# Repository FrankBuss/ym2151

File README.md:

# YM2151 board for C64 and Arduino

## Original Z80 project
https://github.com/kuninet/Z80_YM2151

## C64 Sound Expander circuit diagram
https://www.c64-wiki.de/images/0/0f/Commodore_Sound_Expander_Schematic_SVG.svg

## Parts
TRS connector: https://www.tme.eu/en/details/acjs-nh35/jack-connectors/amphenol/

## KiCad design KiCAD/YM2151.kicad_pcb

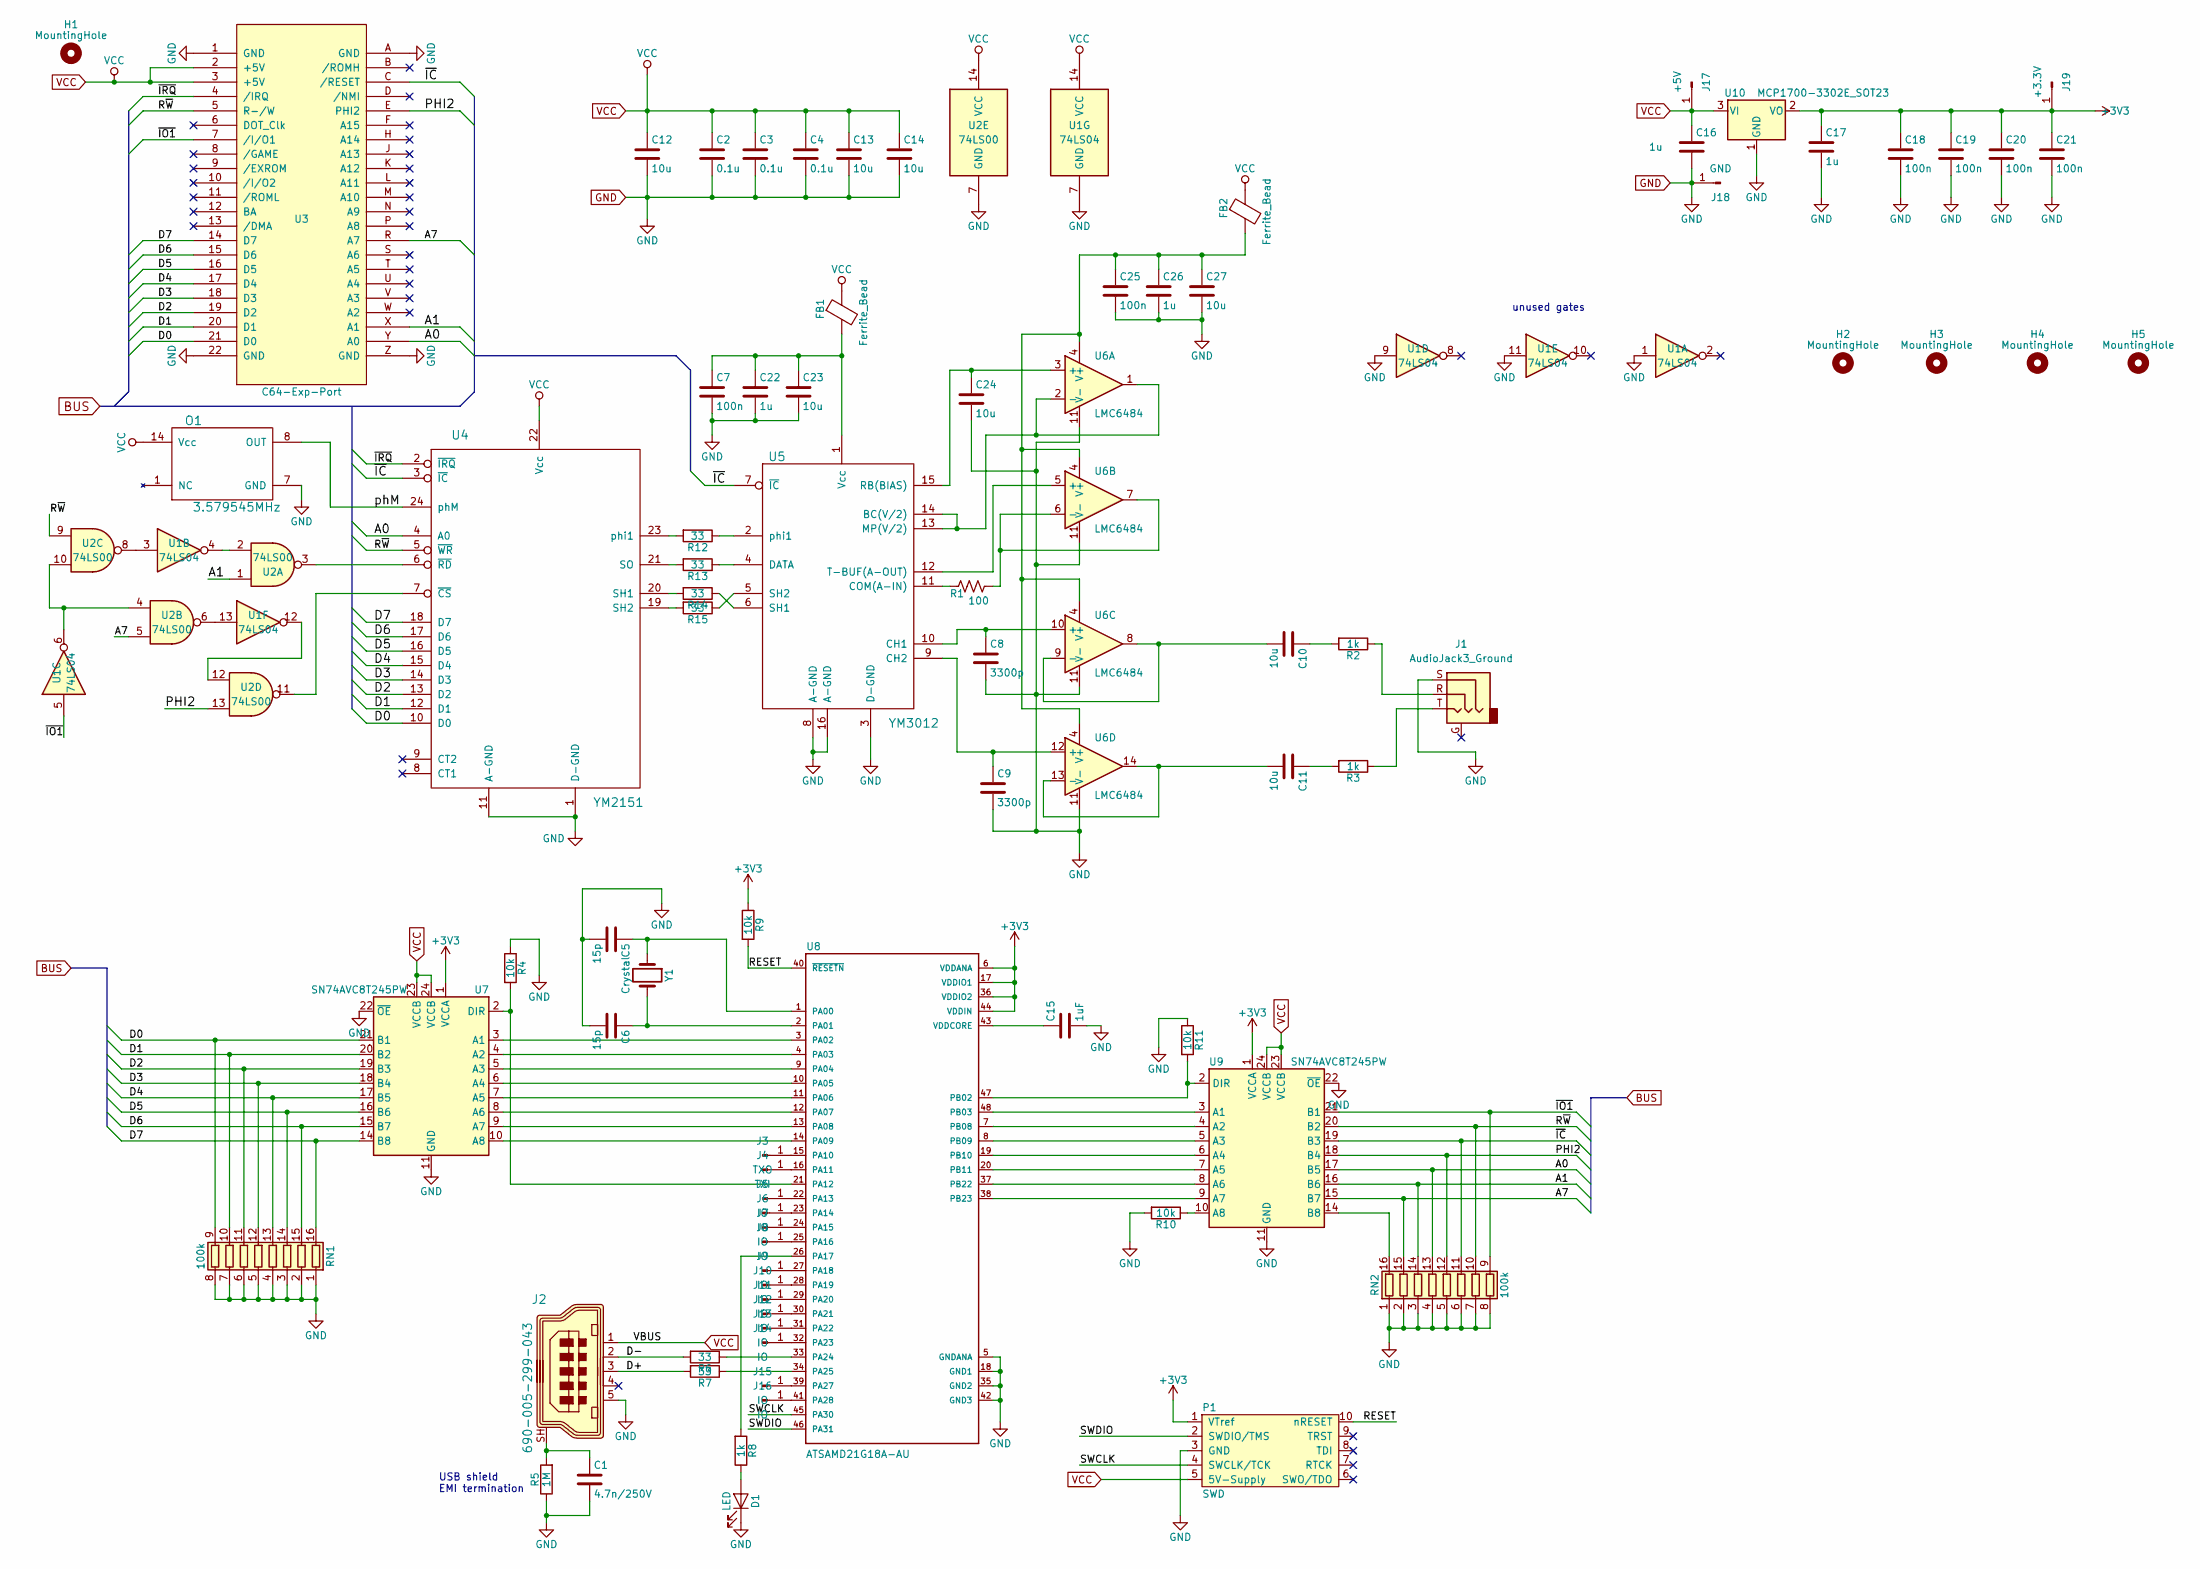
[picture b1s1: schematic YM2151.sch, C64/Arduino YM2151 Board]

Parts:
C1: 4.7n/250V; C_0805_2012Metric
C2, C3, C4: 0.1u; C_0805_2012Metric
C5, C6: 15p; C_0805_2012Metric
C7, C18, C19, C20, C21, C25: 100n; C_0805_2012Metric
C8, C9: 3300p; C_0805_2012Metric
C10, C11, C12, C13, C14, C23, C24, C27: 10u; C_0805_2012Metric
C15: 1uF; C_0805_2012Metric
C16, C17, C22, C26: 1u; C_0805_2012Metric
D1: LED; LED_0805_2012Metric
FB1, FB2: Ferrite_Bead; L_1206_3216Metric
H1, H2, H3, H4, H5: MountingHole; MountingHole_3.2mm_M3
J1: AudioJack3_Ground; trs
J2: 690-005-299-043; USB_Mini_B_Female_690-005-299-043; MPN 690-005-299-043; Digi-Key_PN 151-1206-1-ND
J3: TXO; PinHeader_1x01_P2.54mm_Vertical
J4: TXI; PinHeader_1x01_P2.54mm_Vertical
J5, J6, J7, J8, J9, J10, J11, J12, J13, J14, J15, J16: IO; PinHeader_1x01_P2.54mm_Vertical
J17: +5V; PinHeader_1x01_P2.54mm_Vertical
J18: GND; PinHeader_1x01_P2.54mm_Vertical
J19: +3.3V; PinHeader_1x01_P2.54mm_Vertical
O1: 3.579545MHz; DIP-14_W7.62mm_Socket_LongPads
P1: SWD; swd
R1: 100; R_0805_2012Metric
R2, R3, R8: 1k; R_0805_2012Metric
R4, R9, R10, R11: 10k; R_0805_2012Metric
R5: 1M; R_0805_2012Metric
R6, R7, R12, R13, R14, R15: 33; R_0805_2012Metric
RN1, RN2: 100k; R_Array_Convex_8x0602
U1: 74LS04; SOIC-14_3.9x8.7mm_P1.27mm
U2: 74LS00; SOIC-14_3.9x8.7mm_P1.27mm
U3: C64-Exp-Port; C64-Cart
U4: YM2151; DIP-24_W15.24mm_LongPads
U5: YM3012; DIP-16_W7.62mm_Socket_LongPads
U6: LMC6484; SOIC-14_3.9x8.7mm_P1.27mm
U7, U9: SN74AVC8T245PW; TSSOP-24_4.4x7.8mm_P0.65mm
U8: ATSAMD21G18A-AU; QFP50P900X900X120-48N
U10: MCP1700-3302E_SOT23; SOT-23
Y1: Crystal; Crystal_SMD_3215-2Pin_3.2x1.5mm

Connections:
+3V3: C17.1, C18.1, C19.1, C20.1, C21.1, J19.1, P1.1 (VTref), R9.1, U7.1 (VCCA), U8.6 (VDDANA), U8.17 (VDDIO1), U8.36 (VDDIO2), U8.44 (VDDIN), U9.1 (VCCA), U10.2 (VO)
/A0: RN2.13 (R4.2), U3.Y (A0), U4.4 (A0), U9.17 (B5)
/A1: RN2.14 (R3.2), U2.1, U3.X (A1), U9.16 (B6)
/A7: RN2.15 (R2.2), U2.5, U3.R (A7), U9.15 (B7)
/D0: RN1.9 (R8.2), U3.21 (D0), U4.10 (D0), U7.21 (B1)
/D1: RN1.10 (R7.2), U3.20 (D1), U4.12 (D1), U7.20 (B2)
/D2: RN1.11 (R6.2), U3.19 (D2), U4.13 (D2), U7.19 (B3)
/D3: RN1.12 (R5.2), U3.18 (D3), U4.14 (D3), U7.18 (B4)
/D4: RN1.13 (R4.2), U3.17 (D4), U4.15 (D4), U7.17 (B5)
/D5: RN1.14 (R3.2), U3.16 (D5), U4.16 (D5), U7.16 (B6)
/D6: RN1.15 (R2.2), U3.15 (D6), U4.17 (D6), U7.15 (B7)
/D7: RN1.16 (R1.2), U3.14 (D7), U4.18 (D7), U7.14 (B8)
/D+: J2.3, R7.2
/D-: J2.2, R6.2
/PHI2: RN2.12 (R5.2), U2.13, U3.E (PHI2), U9.18 (B4)
/RESET: P1.10 (nRESET), R9.2, U8.40 (~RESETN~)
/R~W: RN2.10 (R7.2), U2.9, U3.5 (R-/W), U4.5 (~WR), U9.20 (B2)
/SWCLK: P1.4 (SWCLK/TCK), U8.45 (PA30)
/SWDIO: P1.2 (SWDIO/TMS), U8.46 (PA31)
/phM: O1.8 (OUT), U4.24 (phM)
/~IC: RN2.11 (R6.2), U3.C (/RESET), U4.3 (~IC), U5.7 (~IC), U9.19 (B3)
/~IO1: RN2.9 (R8.2), U1.5, U3.7 (/I/O1), U9.21 (B1)
/~IRQ: U3.4 (/IRQ), U4.2 (~IRQ)
GND: C1.2, C2.2, C3.2, C4.2, C5.2, C6.2, C7.2, C8.2, C9.2, C12.2, C13.2, C14.2, C15.2, C16.2, C17.2, C18.2, C19.2, C20.2, C21.2, C22.2, C23.2, C24.2, C25.2, C26.2, C27.2, D1.1 (K), J1.S, J2.5, J18.1, O1.7 (GND), P1.3 (GND), R4.1, R5.1, R10.2, R11.1, RN1.1 (R1.1), RN1.2 (R2.1), RN1.3 (R3.1), RN1.4 (R4.1), RN1.5 (R5.1), RN1.6 (R6.1), RN1.7 (R7.1), RN1.8 (R8.1), RN2.1 (R1.1), RN2.2 (R2.1), RN2.3 (R3.1), RN2.4 (R4.1), RN2.5 (R5.1), RN2.6 (R6.1), RN2.7 (R7.1), RN2.8 (R8.1), U1.1, U1.7 (GND), U1.9, U1.11, U2.7 (GND), U3.1 (GND), U3.22 (GND), U3.A (GND), U3.Z (GND), U4.1 (D-GND), U4.11 (A-GND), U5.3 (D-GND), U5.8 (A-GND), U5.16 (A-GND), U6.11 (V-), U7.11 (GND), U7.12 (GND), U7.13 (GND), U7.22 (~OE), U8.5 (GNDANA), U8.18 (GND1), U8.35 (GND2), U8.42 (GND3), U9.11 (GND), U9.12 (GND), U9.13 (GND), U9.22 (~OE), U10.1 (GND)
unnamed: C1.1, J2.SH, R5.2
unnamed: C5.1, U8.1 (PA00), Y1.1
unnamed: C6.1, U8.2 (PA01), Y1.2
unnamed: C8.1, U5.10 (CH1), U6.10 (+)
unnamed: C9.1, U5.9 (CH2), U6.12 (+)
unnamed: C10.1, R2.2
unnamed: C10.2, U6.8, U6.9 (-)
unnamed: C11.1, R3.2
unnamed: C11.2, U6.13 (-), U6.14
unnamed: C15.1, U8.43 (VDDCORE)
unnamed: C7.1, C22.1, C23.1, FB1.2, U5.1 (Vcc)
unnamed: C24.1, U5.15 (RB(BIAS)), U6.3 (+)
unnamed: C25.1, C26.1, C27.1, FB2.2, U6.4 (V+)
unnamed: D1.2 (A), R8.1
unnamed: J1.R, R2.1
unnamed: J1.T, R3.1
unnamed: J3.1, U8.15 (PA10)
unnamed: J4.1, U8.16 (PA11)
unnamed: J5.1, U8.22 (PA13)
unnamed: J6.1, U8.23 (PA14)
unnamed: J7.1, U8.24 (PA15)
unnamed: J8.1, U8.25 (PA16)
unnamed: J9.1, U8.27 (PA18)
unnamed: J10.1, U8.28 (PA19)
unnamed: J11.1, U8.29 (PA20)
unnamed: J12.1, U8.30 (PA21)
unnamed: J13.1, U8.31 (PA22)
unnamed: J14.1, U8.32 (PA23)
unnamed: J15.1, U8.39 (PA27)
unnamed: J16.1, U8.41 (PA28)
unnamed: R1.1, U6.6 (-), U6.7
unnamed: R1.2, U5.11 (COM(A-IN))
unnamed: R4.2, U7.2 (DIR), U8.21 (PA12)
unnamed: R6.1, U8.33 (PA24)
unnamed: R7.1, U8.34 (PA25)
unnamed: R8.2, U8.26 (PA17)
unnamed: R10.1, U9.10 (A8)
unnamed: R11.2, U8.47 (PB02), U9.2 (DIR)
unnamed: R12.1, U5.2 (phi1)
unnamed: R12.2, U4.23 (phi1)
unnamed: R13.1, U5.4 (DATA)
unnamed: R13.2, U4.21 (SO)
unnamed: R14.1, U5.6 (SH1)
unnamed: R14.2, U4.20 (SH1)
unnamed: R15.1, U5.5 (SH2)
unnamed: R15.2, U4.19 (SH2)
unnamed: RN2.16 (R1.2), U9.14 (B8)
unnamed: U1.3, U2.8
unnamed: U1.4, U2.2
unnamed: U1.6, U2.4, U2.10
unnamed: U1.12, U2.12
unnamed: U1.13, U2.6
unnamed: U2.3, U4.6 (~RD)
unnamed: U2.11, U4.7 (~CS)
unnamed: U5.12 (T-BUF(A-OUT)), U6.5 (+)
unnamed: U5.13 (MP(V/2)), U5.14 (BC(V/2)), U6.1, U6.2 (-)
unnamed: U7.3 (A1), U8.3 (PA02)
unnamed: U7.4 (A2), U8.4 (PA03)
unnamed: U7.5 (A3), U8.9 (PA04)
unnamed: U7.6 (A4), U8.10 (PA05)
unnamed: U7.7 (A5), U8.11 (PA06)
unnamed: U7.8 (A6), U8.12 (PA07)
unnamed: U7.9 (A7), U8.13 (PA08)
unnamed: U7.10 (A8), U8.14 (PA09)
unnamed: U8.7 (PB08), U9.4 (A2)
unnamed: U8.8 (PB09), U9.5 (A3)
unnamed: U8.19 (PB10), U9.6 (A4)
unnamed: U8.20 (PB11), U9.7 (A5)
unnamed: U8.37 (PB22), U9.8 (A6)
unnamed: U8.38 (PB23), U9.9 (A7)
unnamed: U8.48 (PB03), U9.3 (A1)
VCC: C2.1, C3.1, C4.1, C12.1, C13.1, C14.1, C16.1, FB1.1, FB2.1, J2.1, J17.1, O1.14 (Vcc), P1.5 (5V-Supply), U1.14 (VCC), U2.14 (VCC), U3.2 (+5V), U3.3 (+5V), U4.22 (Vcc), U7.23 (VCCB), U7.24 (VCCB), U9.23 (VCCB), U9.24 (VCCB), U10.3 (VI)

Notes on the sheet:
unused gates
USB shield EMI termination

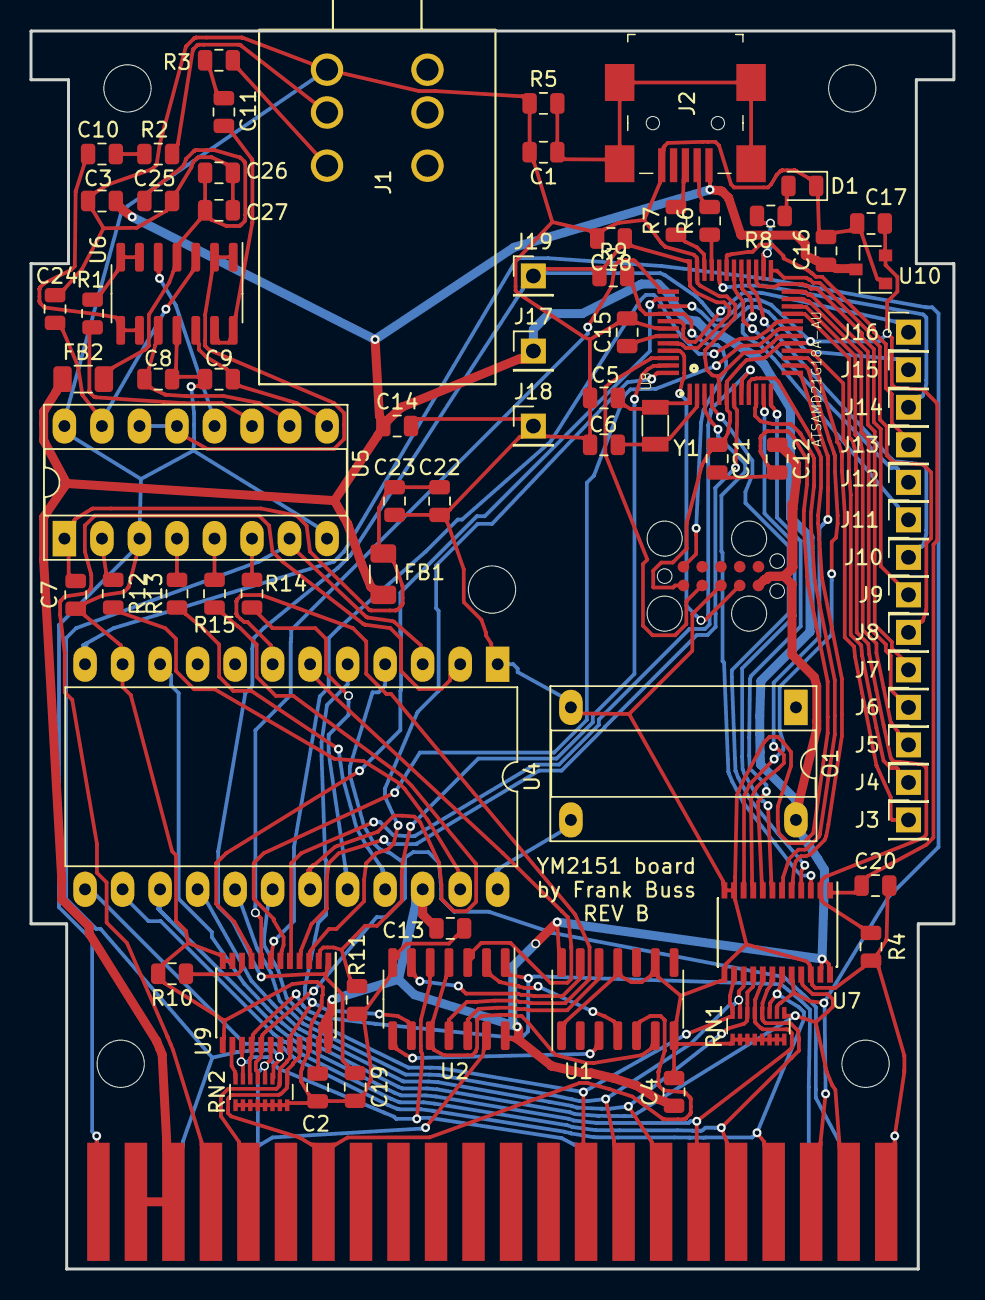
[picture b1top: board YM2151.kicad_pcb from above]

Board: 2 copper layers, 62.5 x 83.8 mm, 84 parts (0 on the bottom side), 96 nets.

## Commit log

2019-10-15 microcontroller added
2019-10-17 board routed
2019-10-17 new PDF export
2019-10-17 final REV A version with gerber files
2019-10-17 KiCad rendering of the board updated
2019-10-24 HTML BOM
2019-10-31 REV B
